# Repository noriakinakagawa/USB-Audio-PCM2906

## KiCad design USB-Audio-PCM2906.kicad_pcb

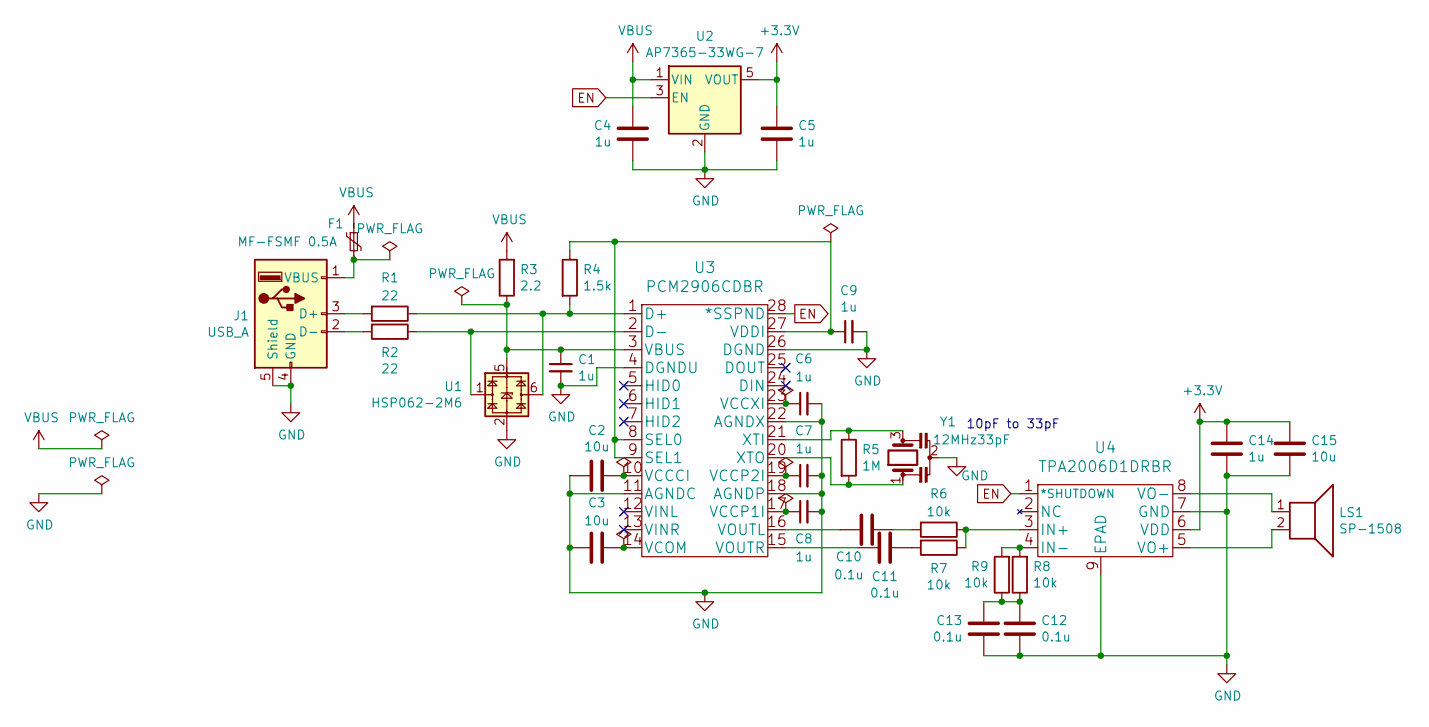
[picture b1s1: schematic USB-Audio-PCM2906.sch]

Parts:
C1, C4, C5, C6, C7, C8, C9, C14: 1u; C_0603
C2, C3, C15: 10u; C_0603
C10, C11, C12, C13: 0.1u; C_0603
F1: MF-FSMF 0.5A; R_0603
J1: USB_A; UP2-AH-1-TH
LS1: SP-1508
R1, R2: 22; R_0603
R3: 2.2; R_0603
R4: 1.5k; R_0603
R5: 1M; R_0603
R6, R7, R8, R9: 10k; R_0603
U1: HSP062-2M6
U2: AP7365-33WG-7; SOT-753
U3: PCM2906CDBR
U4: TPA2006D1DRBR
Y1: 12MHz33pF; CSTNE12M0G550000R0

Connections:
+3V3: C5.1, C14.1, C15.1, U2.5 (VOUT), U4.6 (VDD)
EN: U2.3 (EN), U3.28 (*SSPND), U4.1 (*SHUTDOWN)
GND: C1.2, C2.1, C3.1, C4.2, C5.2, C6.2, C7.2, C8.2, C9.2, C12.1, C13.1, C14.2, C15.2, J1.4 (GND), J1.5 (Shield), U1.2, U2.2 (GND), U3.4 (DGNDU), U3.11 (AGNDC), U3.18 (AGNDP), U3.22 (AGNDX), U3.26 (DGND), U4.7 (GND), U4.9 (EPAD), Y1.2
unnamed: C1.1, R3.1, U1.5, U3.3 (VBUS)
unnamed: C2.2, U3.10 (VCCCI)
unnamed: C3.2, U3.14 (VCOM)
unnamed: C6.1, U3.23 (VCCXI)
unnamed: C7.1, U3.19 (VCCP2I)
unnamed: C8.1, U3.17 (VCCP1I)
unnamed: C9.1, R4.1, U3.8 (SEL0), U3.9 (SEL1), U3.27 (VDDI)
unnamed: C10.1, R6.2
unnamed: C10.2, U3.16 (VOUTL)
unnamed: C11.1, U3.15 (VOUTR)
unnamed: C11.2, R7.2
unnamed: C12.2, C13.2, R8.1, R9.1
unnamed: F1.2, J1.1 (VBUS)
unnamed: J1.2 (D-), R2.2
unnamed: J1.3 (D+), R1.2
unnamed: LS1.1, U4.8 (VO-)
unnamed: LS1.2, U4.5 (VO+)
unnamed: R1.1, R4.2, U1.6, U3.1 (D+)
unnamed: R2.1, U1.1, U3.2 (D-)
unnamed: R5.1, U3.21 (XTI), Y1.3
unnamed: R5.2, U3.20 (XTO), Y1.1
unnamed: R6.1, R7.1, U4.3 (IN+)
unnamed: R8.2, R9.2, U4.4 (IN-)
VBUS: C4.1, F1.1, R3.2, U2.1 (VIN)

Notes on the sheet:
10pF to 33pF

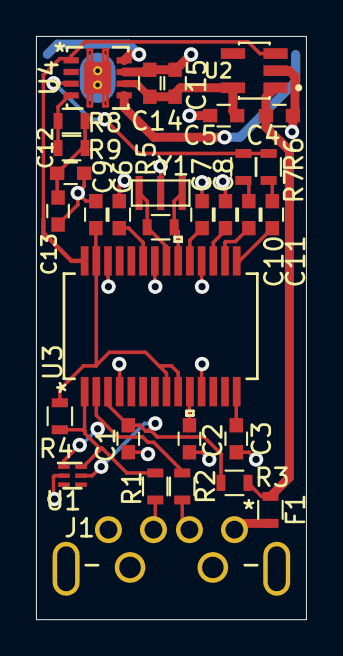
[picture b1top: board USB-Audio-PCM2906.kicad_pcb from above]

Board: 2 copper layers, 15.0 x 32.4 mm, 32 parts (1 on the bottom side), 27 nets.

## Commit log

2021-01-24 Add upload Case
